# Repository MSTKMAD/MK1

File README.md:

# MK1

Migracion desde Bitbucket del repostorio de la Machete MK1

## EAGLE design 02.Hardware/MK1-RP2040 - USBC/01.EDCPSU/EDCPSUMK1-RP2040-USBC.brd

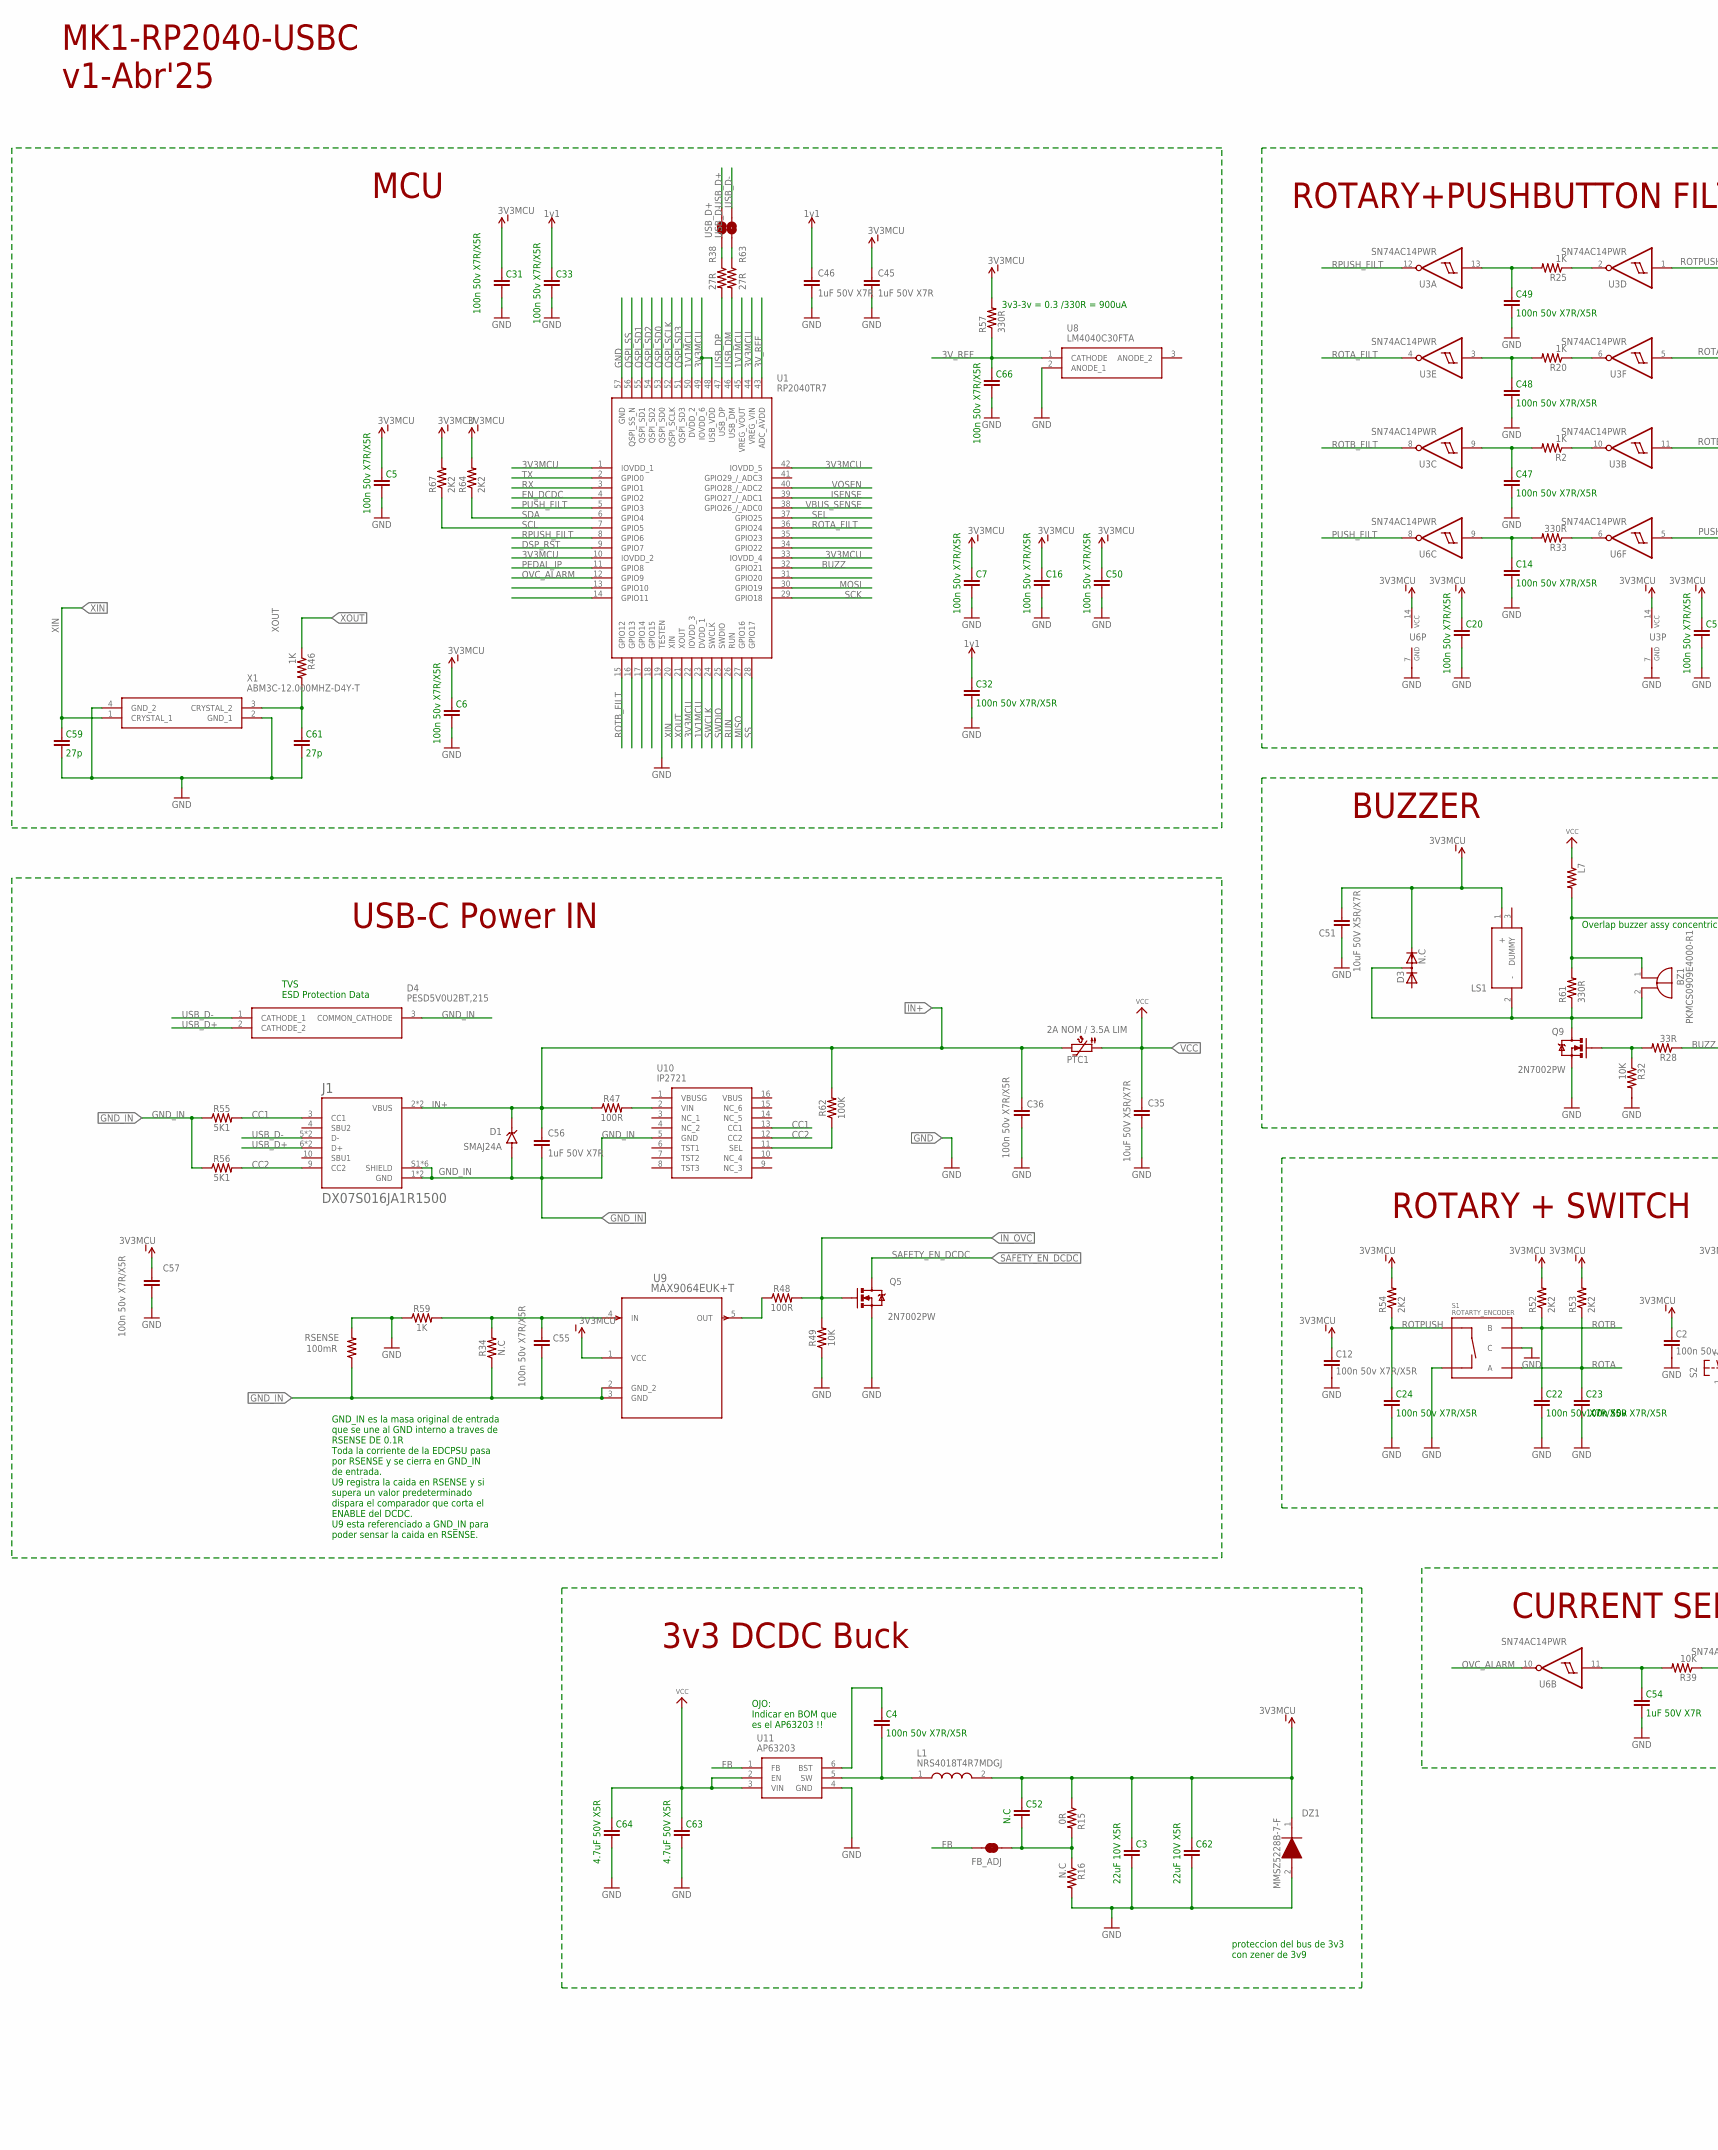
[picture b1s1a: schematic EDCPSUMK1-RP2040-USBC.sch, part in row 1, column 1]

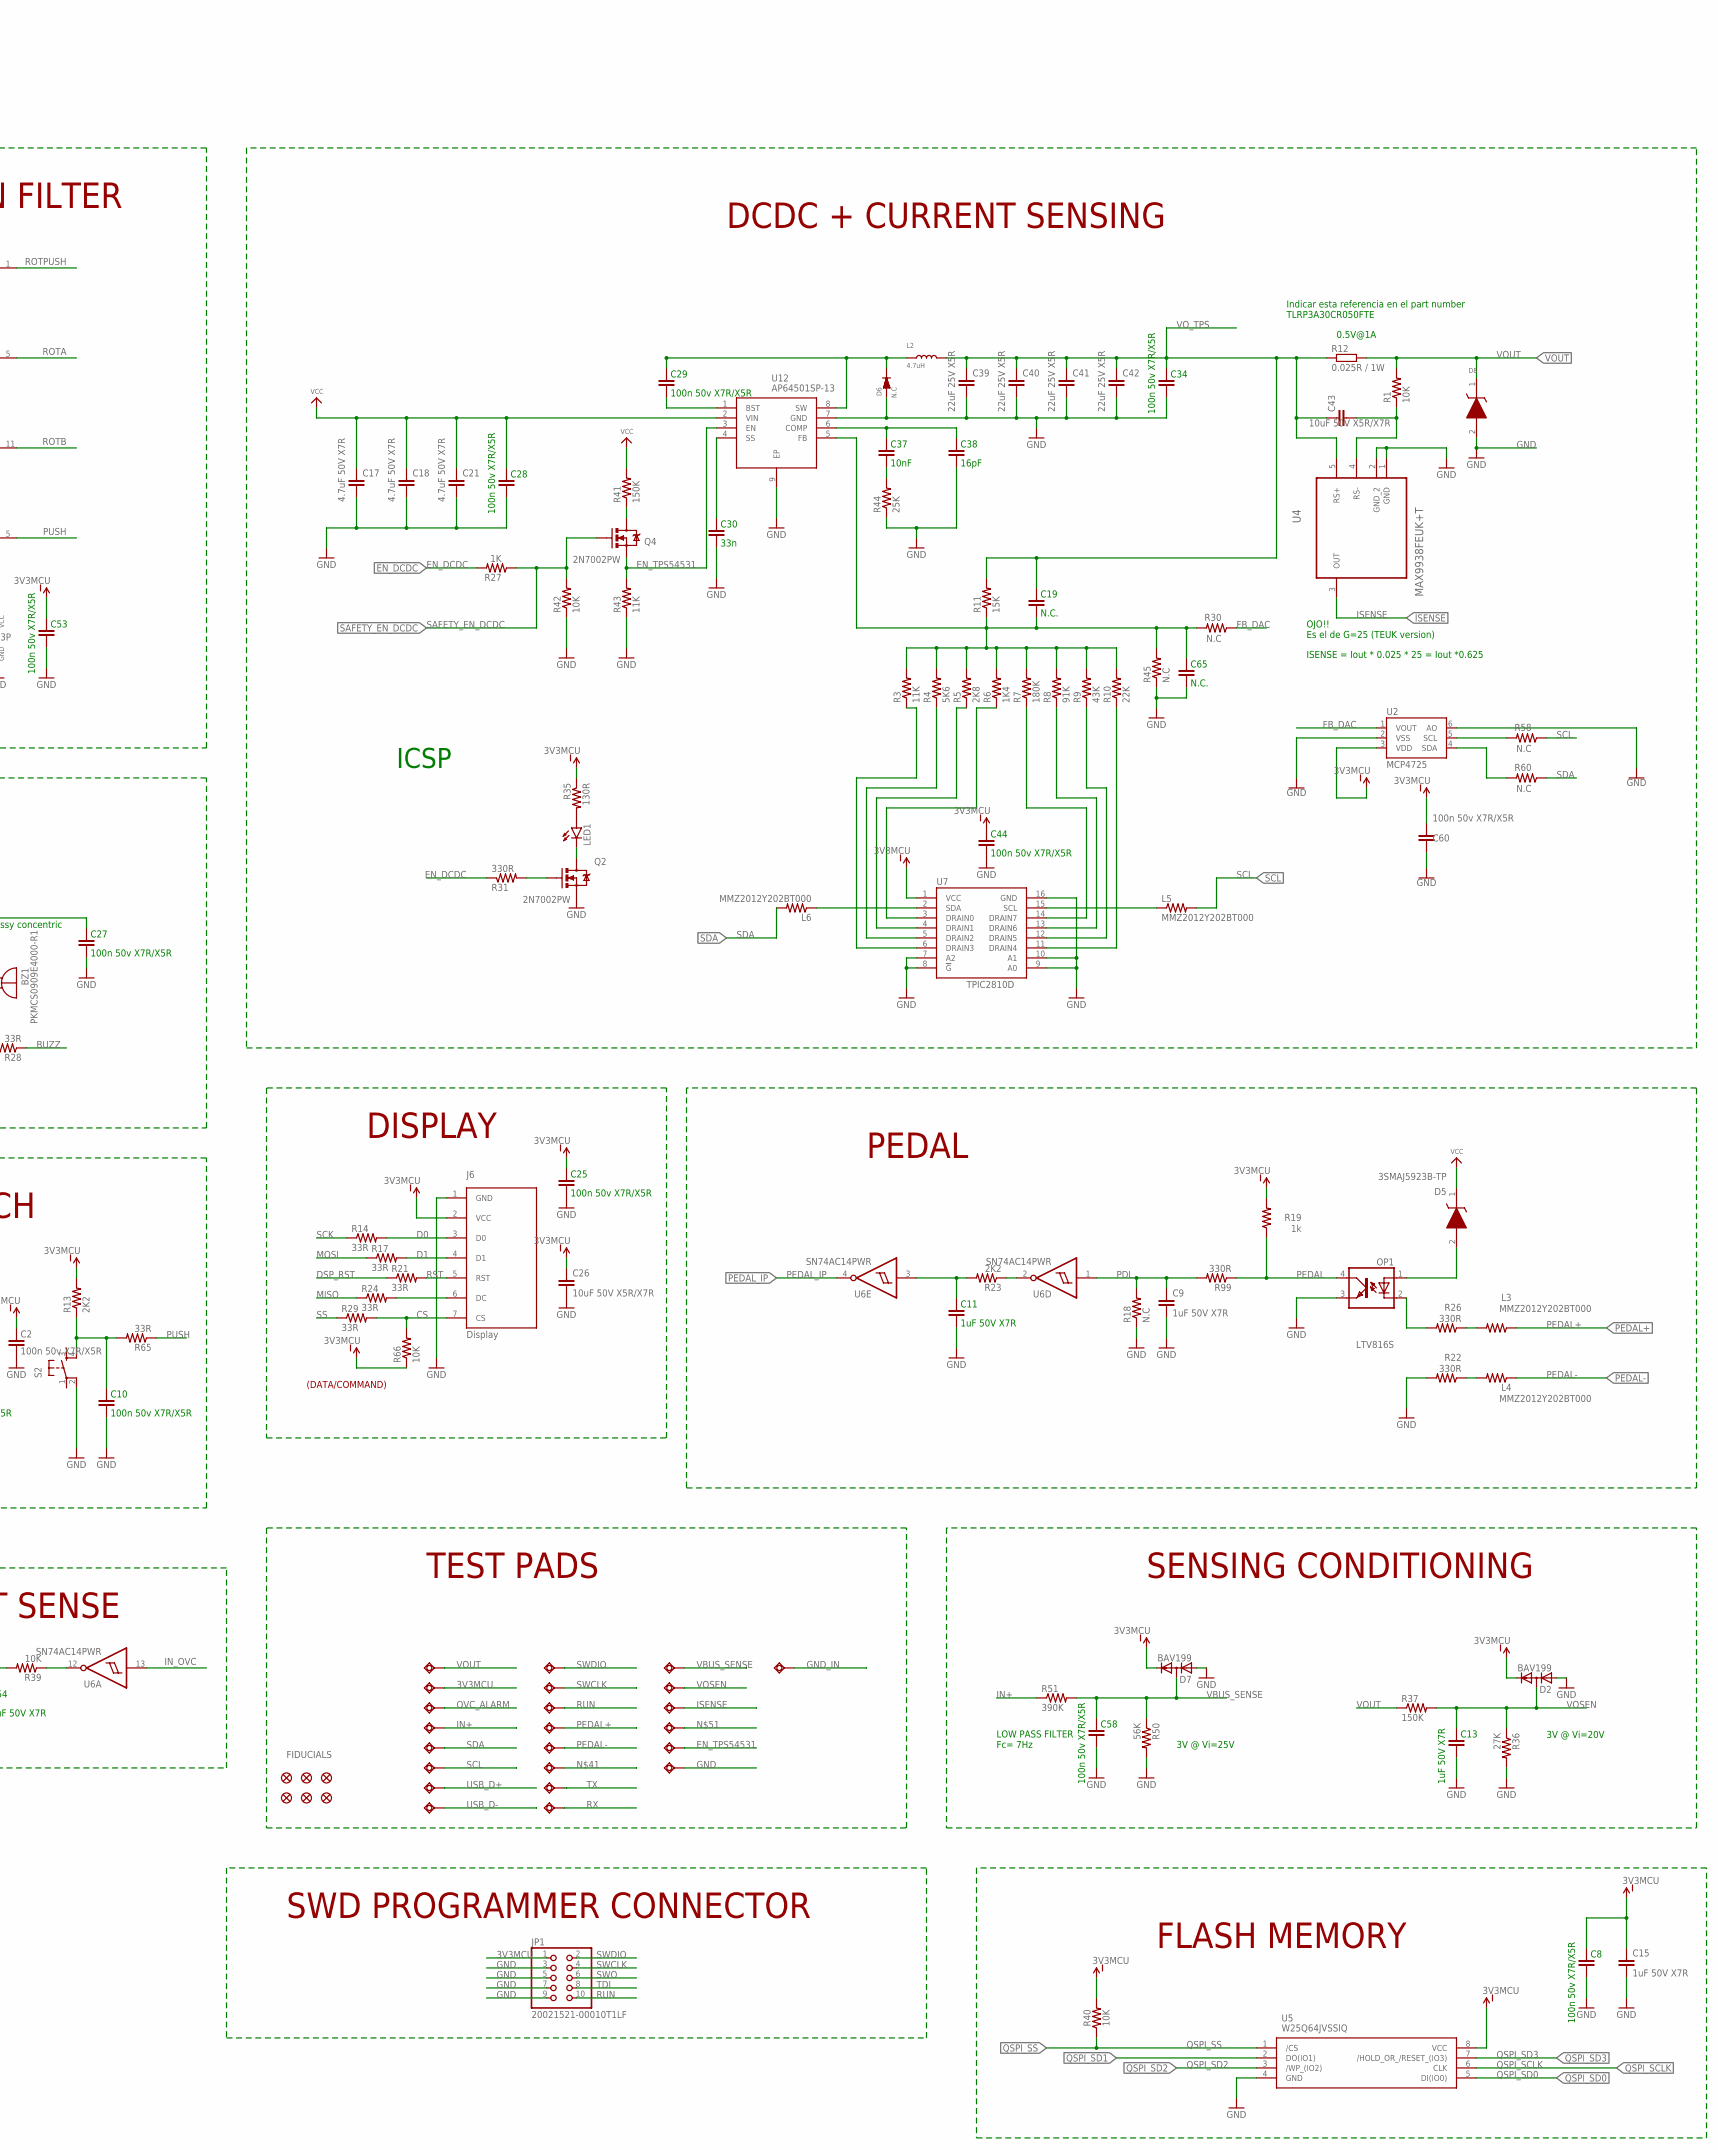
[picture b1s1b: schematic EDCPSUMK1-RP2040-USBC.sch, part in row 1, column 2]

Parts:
3V3MCU: TESTPAD_TPSQB1,27; TESTPAD_B1,27
BZ1: PKMCS0909E4000-R1; PKMCS0909
C2, C4, C5, C6, C7, C8, C10, C12, C14, C16, C20, C22, C23, C24, C25, C27, C28, C29, C31, C32, C33, C34, C36, C44, C47, C48, C49, C50, C53, C55, C57, C58, C60, C66: 100n 50v X7R/X5R; 0805
C3, C62: 22uF 10V X5R; 0805
C9, C11, C13, C15, C45, C46, C54, C56: 1uF 50V X7R; 0805
C17, C18, C21: 4.7uF 50V X7R; 1210
C19, C65: N.C.; 0805
C26, C35, C43, C51: 10uF 50V X5R/X7R; 1206
C30: 33n; 0805
C37: 10nF; 0805
C38: 16pF; 0805
C39, C40, C41, C42: 22uF 25V X5R; 1210
C52: N.C; 0805
C59, C61: 27p; 0805
C63, C64: 4.7uF 50V X5R; 0805
D1: SMAJ24A; DIOM4325X244N
D2, D7: BAV199; SOT23
D3: N.C; SOT23
D4: PESD5V0U2BT,215; SOT95P230X110-3N
D5: 3SMAJ5923B-TP; DIOM5226X244N
D6: N.C; DO-214AB
D8: RB060M-60TR; DIOM5226X244N
DZ1: MMSZ5228B-7-F; SODFL3518X115N
EN_TPS54531: TESTPAD_TPSQB1,27; TESTPAD_B1,27
FB_ADJ: JUMPER-SMT_2_NC_TRACE_NO-SILK; SMT-JUMPER_2_NC_TRACE_NO-SILK
FID1, FID2, FID3, FID4, FID5, FID6: FIDUCIAL1X2; FIDUCIAL-1X2
GND: TESTPAD_TPSQB1,27; TESTPAD_B1,27
GND_IN: TESTPAD_TPSQB1,27; TESTPAD_B1,27
IN+: TESTPAD_TPSQB1,27; TESTPAD_B1,27
ISENSE: TESTPAD_TPSQB1,27; TESTPAD_B1,27
J1: DX07S016JA1R1500; JAE_DX07S016JA1R1500
J6: Display; OLED_LCD
JP1: 20021521-00010T1LF
L1: NRS4018T4R7MDGJ; NRS4018T100MDGJ
L2: 4.7uH; WE-LHMI
L3, L4, L5, L6, L7: MMZ2012Y202BT000; 0805
LED1: LED3MM
LS1: SMT-0540-S-R; SMT0540SR
N$41, N$51: TESTPAD_TPSQB1,27; TESTPAD_B1,27
OP1: LTV816S; SMD4
OVC_ALARM: TESTPAD_TPSQB1,27; TESTPAD_B1,27
PEDAL+: TESTPAD_TPSQB1,27; TESTPAD_B1,27
PEDAL-: TESTPAD_TPSQB1,27; TESTPAD_B1,27
PTC1: 2A NOM / 3.5A LIM; 1812L
Q2, Q4, Q5, Q9: 2N7002PW; SOT323
R1, R32, R39, R40, R42, R49, R66: 10K; 0805
R2, R20, R25, R27, R46, R59: 1K; 0805
R3, R43: 11K; 0805
R4: 5K6; 0805
R5: 2K8; 0805
R6: 1K4; 0805
R7: 180K; 0805
R8: 91K; 0805
R9: 43K; 0805
R10: 22K; 0805
R11: 15K; 0805
R12: 0.025R / 1W; R2512
R13, R23, R52, R53, R54, R64, R67: 2K2; 0805
R14, R17, R21, R24, R28, R29, R65: 33R; 0805
R15: 0R; 0805
R16, R18, R30, R34, R45, R58, R60: N.C; 0805
R19: 1k; 0805
R22, R26, R31, R33, R57, R61, R99: 330R; 0805
R35: 130R; 0805
R36: 27K; 0805
R37, R41: 150K; 0805
R38, R63: 27R; 0805
R44: 25K; 0805
R47, R48: 100R; 0805
R50: 56K; 0805
R51: 390K; 0805
R55, R56: 5K1; 0805
R62: 100K; 0805
RSENSE: 100mR; 1206
RUN: TESTPAD_TPSQB1,27; TESTPAD_B1,27
RX: TESTPAD_TPSQB1,27; TESTPAD_B1,27
S1: ROTARTY_ENCODER; ROTARY_ENC_PLAIN
S2: TAC_SWITCH_KSC931G-SMD; TAC_SW_SMD_KSC931G
SCL: TESTPAD_TPSQB1,27; TESTPAD_B1,27
SDA: TESTPAD_TPSQB1,27; TESTPAD_B1,27
SWCLK: TESTPAD_TPSQB1,27; TESTPAD_B1,27
SWDIO: TESTPAD_TPSQB1,27; TESTPAD_B1,27
TX: TESTPAD_TPSQB1,27; TESTPAD_B1,27
U1: RP2040TR7
U2: MCP4725; SOT23-6
U3, U6: SN74AC14PWR; TSSOP14
U4: MAX9938FEUK+T; SOT95P280X145-5N
U5: W25Q64JVSSIQ; SOIC127P790X216-8N
U7: TPIC2810D; SO16
U8: LM4040C30FTA; SOT96P240X120-3N
U9: MAX9064EUK+T; 21-0057F_MXM
U10: IP2721; SOP65P640X120-16N
U11: AP63203; SOT95P280X100-6N
U12: AP64501SP-13; SOIC127P600X163-9N
USB-D+: TESTPAD_TPSQB1,27; TESTPAD_B1,27
USB-D-: TESTPAD_TPSQB1,27; TESTPAD_B1,27
USB_D+: JUMPER-SMT_2_NO_NO-SILK; SMT-JUMPER_2_NO_NO-SILK
USB_D-: JUMPER-SMT_2_NO_NO-SILK; SMT-JUMPER_2_NO_NO-SILK
VBUS_SENSE: TESTPAD_TPSQB1,27; TESTPAD_B1,27
VOSEN: TESTPAD_TPSQB1,27; TESTPAD_B1,27
VOUT: TESTPAD_TPSQB1,27; TESTPAD_B1,27
X1: ABM3C-12.000MHZ-D4Y-T; ABM3C16000MHZD4YT

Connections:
1V1MCU: C32.2, C33.2, C46.1, U1.23 (DVDD_1), U1.45 (VREG_VOUT), U1.50 (DVDD_2)
3V3MCU: 3V3MCU.TP, C2.2, C3.2, C5.2, C6.2, C7.2, C8.2, C12.2, C15.1, C16.2, C20.2, C25.2, C26.1, C31.2, C44.2, C45.1, C50.2, C51.2, C52.2, C53.2, C57.1, C60.2, C62.2, D2.2 (C), D3.2 (C), D7.2 (C), DZ1.1 (K), J6.2 (VCC), JP1.1, L1.2, LS1.1 (+), R13.2, R15.1, R19.2, R35.1, R40.2, R52.2, R53.2, R54.2, R57.2, R64.2, R66.1, R67.2, U1.1 (IOVDD_1), U1.10 (IOVDD_2), U1.22 (IOVDD_3), U1.33 (IOVDD_4), U1.42 (IOVDD_5), U1.44 (VREG_VIN), U1.48 (USB_VDD), U1.49 (IOVDD_6), U2.3 (VDD), U3.14 (VCC), U5.8 (VCC), U6.14 (VCC), U7.1 (VCC), U9.1 (VCC)
3V_REF: C66.2, R57.1, U1.43 (ADC_AVDD), U8.1 (CATHODE)
BUZZ: R28.1, U1.32 (GPIO21)
CC1: J1.3 (CC1), R55.2, U10.13 (CC1)
CC2: J1.9 (CC2), R56.2, U10.12 (CC2)
CS: J6.7 (CS), R29.2, R66.2
D0: J6.3 (D0), R14.2
D1: J6.4 (D1), R17.2
DSP_RST: R21.1, U1.9 (GPIO7)
EN_DCDC: R27.2, R31.1, U1.4 (GPIO2)
EN_TPS54531: EN_TPS54531.TP, Q4.2 (S), R43.2, U12.3 (EN)
FB: FB_ADJ.2, U11.1 (FB)
FB_DAC: R30.1, U2.1 (VOUT)
GND: C2.1, C3.1, C5.1, C6.1, C7.1, C8.1, C9.2, C10.1, C11.1, C12.1, C13.1, C14.1, C15.2, C16.1, C17.2, C18.2, C20.1, C21.2, C22.1, C23.1, C24.1, C25.1, C26.2, C27.1, C28.1, C30.1, C31.1, C32.1, C33.1, C34.1, C35.2, C36.1, C38.1, C39.2, C40.2, C41.2, C42.2, C44.1, C45.2, C46.2, C47.1, C48.1, C49.1, C50.1, C51.1, C53.1, C54.1, C57.2, C58.1, C59.1, C60.1, C61.1, C62.1, C63.1, C64.1, C65.1, C66.1, D2.1 (A), D6.1 (A), D7.1 (A), D8.2 (A), DZ1.2 (A), GND.TP, J6.1 (GND), JP1.3, JP1.5, JP1.7, JP1.9, OP1.3 (EMIT), Q2.2 (S), Q5.2 (S), Q9.2 (S), R16.2, R18.1, R22.2, R32.2, R36.2, R42.1, R43.1, R44.1, R45.1, R49.1, R50.2, R59.1, RSENSE.2, S1.C, S1.SW-, S2.2, U1.19 (TESTEN), U1.57 (GND), U2.2 (VSS), U2.6 (AO), U3.7 (GND), U4.1 (GND), U4.2 (GND_2), U5.4 (GND), U6.7 (GND), U7.7 (A2), U7.8 (!G), U7.9 (A0), U7.10 (A1), U7.16 (GND), U8.2 (ANODE_1), U11.4 (GND), U12.7 (GND), U12.9 (EP), X1.2 (GND_1), X1.4 (GND_2)
GND_IN: C55.2, C56.2, D1.A, D4.3 (COMMON_CATHODE), GND_IN.TP, J1.1 (GND), J1.12 (GND), J1.S1 (SHIELD), J1.S2 (SHIELD), J1.S3 (SHIELD), J1.S4 (SHIELD), J1.S5 (SHIELD), J1.S6 (SHIELD), R34.1, R55.1, R56.1, RSENSE.1, U9.2 (GND_2), U9.3 (GND), U10.5 (GND)
IN+: C36.2, C56.1, D1.C (K), IN+.TP, J1.2 (VBUS), J1.11 (VBUS), PTC1.2, R47.1, R51.1, R62.2
IN_OVC: Q5.1 (G), R48.2, R49.2, U6.13 (I)
ISENSE: ISENSE.TP, U1.39 (GPIO27_/_ADC1), U4.3 (OUT)
MISO: R24.1, U1.27 (GPIO16)
MOSI: R17.1, U1.30 (GPIO19)
unnamed: R3.1, U7.6 (DRAIN3)
unnamed: R4.1, U7.5 (DRAIN2)
unnamed: R5.1, U7.4 (DRAIN1)
unnamed: R6.1, U7.3 (DRAIN0)
unnamed: R7.1, U7.14 (DRAIN7)
unnamed: J6.6 (DC), R24.2
unnamed: R8.1, U7.13 (DRAIN6)
unnamed: R9.1, U7.12 (DRAIN5)
unnamed: R10.1, U7.11 (DRAIN4)
unnamed: C43.2, R1.1, U4.4 (RS-)
unnamed: LED1.A, R35.2
unnamed: LED1.K (C), Q2.3 (D)
unnamed: R33.1, U6.6 (O)
unnamed: R62.1, U10.11 (SEL)
unnamed: R39.1, U6.12 (O)
unnamed: D5.2 (A), OP1.1 (A)
unnamed: C10.2, R13.1, R65.2, S2.4
unnamed: C47.2, R2.2, U3.9 (I)
unnamed: C19.1, C65.2, R3.2, R4.2, R5.2, R6.2, R7.2, R8.2, R9.2, R10.2, R11.1, R30.2, R45.2, U12.5 (FB)
unnamed: Q9.1 (G), R28.2, R32.1
unnamed: Q2.1 (G), R31.2
unnamed: R2.1, U3.10 (O)
unnamed: R20.1, U3.6 (O)
unnamed: R25.1, U3.2 (O)
unnamed: C49.2, R25.2, U3.13 (I)
unnamed: C48.2, R20.2, U3.3 (I)
unnamed: C11.2, R23.2, U6.3 (I)
unnamed: BZ1.2 (-), D3.3 (AC), LS1.2 (-), Q9.3 (D), R61.1
unnamed: BZ1.1 (+), C27.2, L7.2, R61.2
unnamed: R23.1, U6.2 (O)
unnamed: Q4.3 (D), R41.1
unnamed: C14.2, R33.2, U6.9 (I)
unnamed: C52.1, FB_ADJ.1, R15.2, R16.1
unnamed: C54.2, R39.2, U6.11 (I)
unnamed: L6.1, U7.2 (SDA)
unnamed: N$41.TP, OP1.2 (C), R26.2
unnamed: L3.2, R26.1
unnamed: C30.2, U12.4 (SS)
unnamed: R58.2, U2.5 (SCL)
unnamed: L4.2, R22.1
unnamed: C29.1, U12.1 (BST)
unnamed: R60.2, U2.4 (SDA)
unnamed: R47.2, U10.2 (VIN)
unnamed: C29.2, D6.2 (K), L2.1, N$51.TP, U12.8 (SW)
unnamed: C37.2, C38.2, U12.6 (COMP)
unnamed: C37.1, R44.2
unnamed: L5.1, U7.15 (SCL)
unnamed: C4.2, U11.6 (BST)
unnamed: R48.1, U9.5 (OUT)
unnamed: C55.1, R34.2, R59.2, U9.4 (IN)
unnamed: C61.2, R46.2, X1.3 (CRYSTAL_2)
unnamed: R38.1, USB_D+.1
unnamed: R63.1, USB_D-.1
unnamed: C4.1, L1.1, U11.5 (SW)
OVC_ALARM: OVC_ALARM.TP, U1.12 (GPIO9), U6.10 (O)
PDL: C9.1, R18.2, R99.2, U6.1 (I)
PEDAL: OP1.4 (COL), R19.1, R99.1
PEDAL+: L3.1, PEDAL+.TP
PEDAL-: L4.1, PEDAL-.TP
PEDAL_IP: U1.11 (GPIO8), U6.4 (O)
PUSH: R65.1, U6.5 (I)
PUSH_FILT: U1.5 (GPIO3), U6.8 (O)
QSPI_SCLK: U1.52 (QSPI_SCLK), U5.6 (CLK)
QSPI_SD0: U1.53 (QSPI_SD0), U5.5 (DI(IO0))
QSPI_SD1: U1.55 (QSPI_SD1), U5.2 (DO(IO1))
QSPI_SD2: U1.54 (QSPI_SD2), U5.3 (/WP_(IO2))
QSPI_SD3: U1.51 (QSPI_SD3), U5.7 (/HOLD_OR_/RESET_(IO3))
QSPI_SS: R40.1, U1.56 (QSPI_SS_N), U5.1 (/CS)
ROTA: C23.2, R53.1, S1.A, U3.5 (I)
ROTA_FILT: U1.36 (GPIO24), U3.4 (O)
ROTB: C22.2, R52.1, S1.B, U3.11 (I)
ROTB_FILT: U1.15 (GPIO12), U3.8 (O)
ROTPUSH: C24.2, R54.1, S1.SW+, U3.1 (I)
RPUSH_FILT: U1.8 (GPIO6), U3.12 (O)
RST: J6.5 (RST), R21.2
RUN: JP1.10, RUN.TP, U1.26 (RUN)
RX: RX.TP, U1.3 (GPIO1)
SAFETY_EN_DCDC: Q4.1 (G), Q5.3 (D), R27.1, R42.2
SCK: R14.1, U1.29 (GPIO18)
SCL: L5.2, R58.1, R67.1, SCL.TP, U1.7 (GPIO5)
SDA: L6.2, R60.1, R64.1, SDA.TP, U1.6 (GPIO4)
SEL: U1.37 (GPIO25)
SS: R29.1, U1.28 (GPIO17)
SWCLK: JP1.4, SWCLK.TP, U1.24 (SWCLK)
SWDIO: JP1.2, SWDIO.TP, U1.25 (SWDIO)
SWO: JP1.6
TDI: JP1.8
TX: TX.TP, U1.2 (GPIO0)
USB_D+: D4.2 (CATHODE_2), J1.6 (D+), J1.7 (D+), USB-D+.TP, USB_D+.2
USB_D-: D4.1 (CATHODE_1), J1.5 (D-), J1.8 (D-), USB-D-.TP, USB_D-.2
USB_DM: R63.2, U1.46 (USB_DM)
USB_DP: R38.2, U1.47 (USB_DP)
VBUS_SENSE: C58.2, D7.3 (AC), R50.1, R51.2, U1.38 (GPIO26_/_ADC0), VBUS_SENSE.TP
VCC: C17.1, C18.1, C21.1, C28.2, C35.1, C63.2, C64.2, D5.1 (K), L7.1, PTC1.1, R41.2, U11.2 (EN), U11.3 (VIN), U12.2 (VIN)
VOSEN: C13.2, D2.3 (AC), R36.1, R37.2, U1.40 (GPIO28_/_ADC2), VOSEN.TP
VOUT: D8.1 (K), R1.2, R12.2, R37.1, VOUT.TP
VO_TPS: C19.2, C34.2, C39.1, C40.1, C41.1, C42.1, C43.1, L2.2, R11.2, R12.1, U4.5 (RS+)
XIN: C59.2, U1.20 (XIN), X1.1 (CRYSTAL_1)
XOUT: R46.1, U1.21 (XOUT)

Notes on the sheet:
0.5V@1A
SENSING CONDITIONING
TEST PADS
MK1-RP2040-USBC v1-Abr'25
(DATA/COMMAND)
Overlap buzzer assy concentric
ICSP
BUZZER
ROTARY + SWITCH
DISPLAY
FIDUCIALS
OJO!! Es el de G=25 (TEUK version)
ISENSE = Iout * 0.025 * 25 = Iout *0.625
3V @ Vi=25V
LOW PASS FILTER Fc= 7Hz
SWD PROGRAMMER CONNECTOR
3v3 DCDC Buck
OJO: Indicar en BOM que es el AP63203 !!
FLASH MEMORY
USB-C Power IN
PEDAL
CURRENT SENSE
ROTARY+PUSHBUTTON FILTER
DCDC + CURRENT SENSING
MCU
Indicar esta referencia en el part number TLRP3A30CR050FTE
3v3-3v = 0.3 /330R = 900uA
TVS ESD Protection Data
GND_IN es la masa original de entrada que se une al GND interno a traves de RSENSE DE 0.1R Toda la corriente de la EDCPSU pasa por RSENSE y se cierra en GND_IN de entrada. U9 registra la caida en RSENSE y si supera un valor predeterminado dispara el comparador que corta el ENABLE del DCDC. U9 esta 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
proteccion del bus de 3v3 con zener de 3v9
3V @ Vi=20V

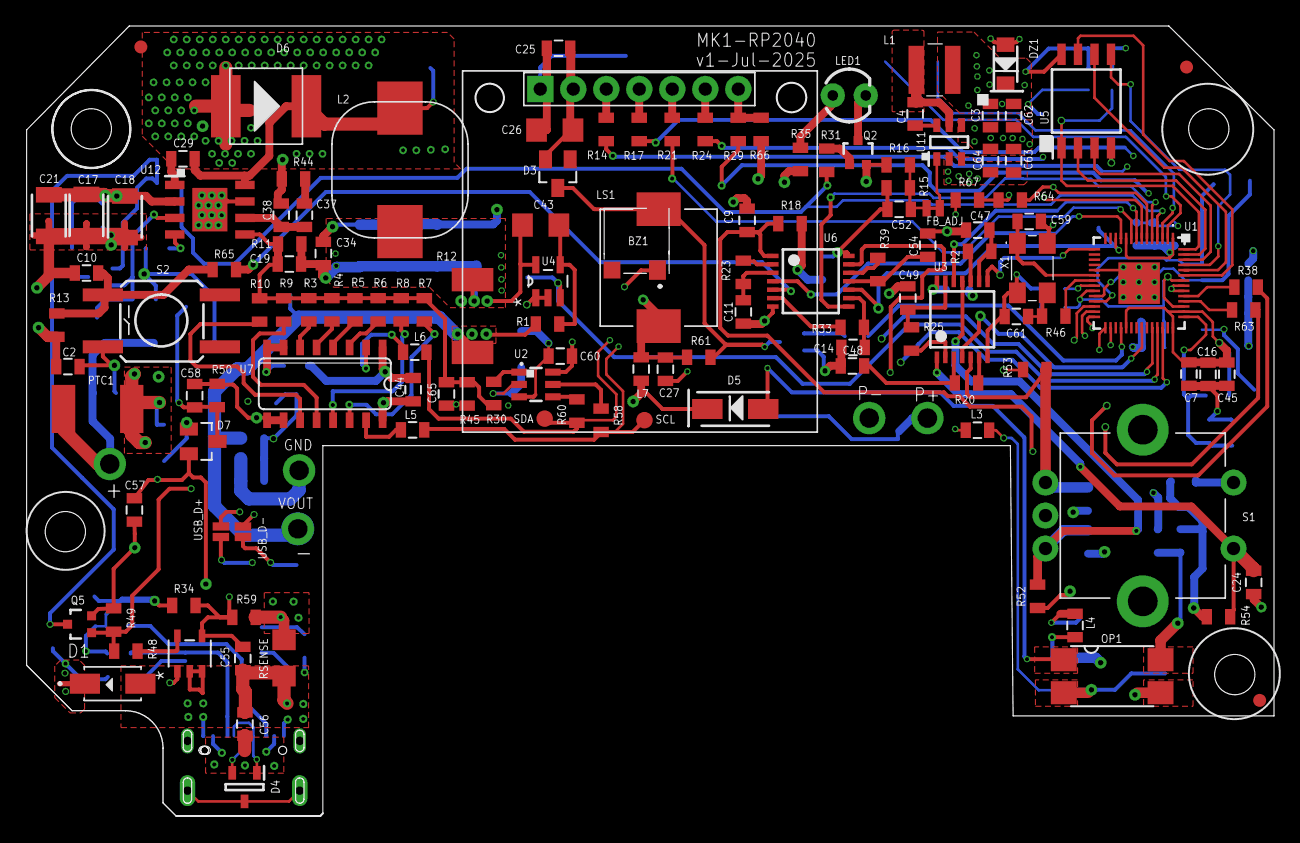
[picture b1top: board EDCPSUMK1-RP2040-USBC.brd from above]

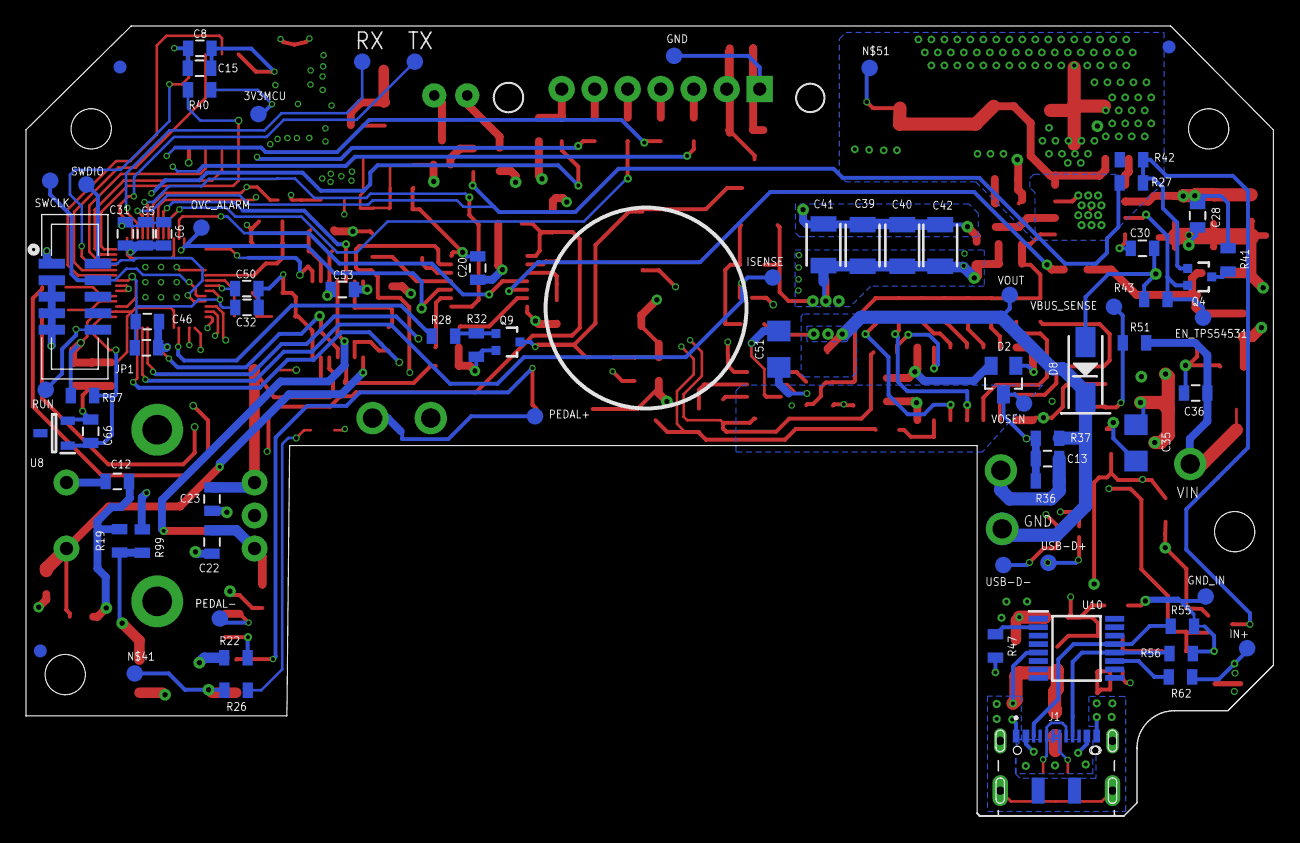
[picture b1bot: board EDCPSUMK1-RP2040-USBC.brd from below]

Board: 4 copper layers, 96.0 x 60.8 mm, 209 parts (76 on the bottom side), 117 nets.

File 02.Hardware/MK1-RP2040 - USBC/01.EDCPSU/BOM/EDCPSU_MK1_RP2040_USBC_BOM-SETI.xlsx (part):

|  |  |  | BOM VERSION v | 1
 |  |  |  | Fecha | 45839
 |  |  |  | MK1-RP2040-USBC
Assembly? | Cambios | Pos | Qty | Parts | Value | Device | Package | Description | Details | COST (500pcs) | COST per Board (500 pcs) | DIGIKEY
P | NO | 1 | 1 | BZ1 | PKMCS0909E4000-R1 | PKMCS0909E4000-R1 | PKMCS0909 | PKMCS0909E4000-R1 |  | 0.48 | 0.48 | https://www.digikey.es/es/products/detail/murata-electronics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
P | NO | 2 | 3 | C17, C18, C21 | 4.7uF 50V X7R | CAP1210 | SMD1210 | Capacitor |  | 0.10598 | 0.31794 | https://www.digikey.es/en/products/detail/samsung-electro-me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
NO | NO | 3 | 0 | C19, C65 | N.C. | CAP0805 | SMD0805 | Capacitor |  |  | 0
P | NO | 4 | 34 | C2, C4, C5, C6, C7, C8, C10, C12, C14, C16, C20, C22, C23, C24, C25, C27, C28, 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 | 100n 50v X7R/X5R | CAP0805 | SMD0805 | Capacitor |  |  | 0
P | NO | 5 | 4 | C26, C35, C43, C51 | 10uF 50V X5R/X7R | CAP1206 | SMD1206 | Capacitor |  | 6.9220000000000004E-2 | 0.27688000000000001 | https://www.digikey.es/en/products/detail/samsung-electro-me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
P | NO | 6 | 2 | C3, C62 | 22uF 10V X5R | CAP0805 | SMD0805 | Capacitor |  | 5.6300000000000003E-2 | 0.11260000000000001 | https://www.digikey.es/en/products/detail/murata-electronics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
P | NO | 7 | 1 | C30 | 33n | CAP0805 | SMD0805 | Capacitor |  |  | 0
P | NO | 8 | 1 | C37 | 10nF | CAP0805 | SMD0805 | Capacitor |  |  | 0
P | NO | 9 | 1 | C38 | 16pF | CAP0805 | SMD0805 | Capacitor |  |  | 0
P | NO | 10 | 4 | C39, C40, C41, C42 | 22uF 25V X5R | CAP1210 | SMD1210 | Capacitor |  | 0.12361999999999999 | 0.49447999999999998 | https://www.digikey.es/en/products/detail/samsung-electro-me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
NO | NO | 11 | 0 | C52 | N.C | CAP0805 | SMD0805 | Capacitor |  |  | 0
P | NO | 12 | 2 | C59, C61 | 27p | CAP0805 | SMD0805 | Capacitor |  |  | 0
P | NO | 13 | 2 | C63, C64 | 4.7uF 50V X5R | CAP0805 | SMD0805 | Capacitor |  | 4.2759999999999999E-2 | 8.5519999999999999E-2 | https://www.digikey.es/en/products/detail/murata-electronics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
P | NO | 14 | 8 | C9, C11, C13, C15, C45, C46, C54, C56 | 1uF 50V X7R | CAP0805 | SMD0805 | Capacitor |  |  | 0
P | NO | 15 | 1 | D1 | SMAJ24A | SMAJ24A | SMA-DO214 | ESD Suppressors / TVS Diodes 24volts 5uA 10.3 Amps UNI-Dir |  | 0.10872 | 0.10872 | https://www.digikey.es/en/products/detail/littelfuse-inc/SMA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
P | NO | 16 | 2 | D2, D7 | BAV199 | BAV199 | SOT23 | DIODE |  | 0.1145 | 0.22900000000000001 | https://www.digikey.es/es/products/detail/infineon-technolog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
P | NO | 17 | 1 | D4 | PESD5V0U2BT,215 | PESD5V0U2BT,215 | SOT23 | PESD5V0U2BT - Ultra low capacitance bidirectional double ESD protection diode |  | 0.17976 | 0.17976 | https://www.digikey.es/es/products/detail/nexperia-usa-inc/P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
P | NO | 18 | 1 | D5 | 3SMAJ5923B-TP | 3SMAJ5923B-TP | SMA-DO214 | Zener Diodes 3W 8.2V |  | 0.1181 | 0.1181 | https://www.digikey.es/es/products/detail/micro-commercial-c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
NO | NO | 19 | 0 | D6 | N.C | DSMC | DO-214AB |  |  |  | 0
P | NO | 20 | 1 | D8 | SMAJ18A | SMAJ18A | SMA-DO214 | TVS 18V 400W Unidirectional |  | 0.12508 | 0.12508 | https://www.digikey.es/en/products/detail/littelfuse-inc/SMA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
P | NO | 21 | 1 | DZ1 | MMSZ5228B | MMSZ5228B | SOD123F | Diode Zener 3.9 5% 500mW 2Pin SOD123 Diodes Inc MMSZ5227B-7-F Zener Diode, 3.9V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 |  | 8.6999999999999994E-2 | 8.6999999999999994E-2 | https://eu.mouser.com/ProductDetail/Diotec-Semiconductor/MMS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
P | NO | 22 | 1 | J1 | DX07S016JA1R1500 | DX07S016JA1R1500 | JAE_DX07S016JA1R1500 | USB-C (USB TYPE-C) USB 2.0 Receptacle Connector 24 (16+8 Dummy) Position Surfac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 |  | 1.0803 | 1.0803 | https://www.digikey.es/es/products/detail/jae-electronics/DX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
P | NO | 23 | 1 | J6 | Display | OLED_LCD | OLED_LCD |  |  |  | 0
P | NO | 24 | 1 | JP1 | 20021521-00010T1LF | 20021521-00010T1LF | 20021521-00010T1LF | MINITEK 127 SHROUDED HDR |  | 0.64117000000000002 | 0.64117000000000002 | https://www.digikey.es/en/products/detail/amphenol-cs-fci/20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
P | NO | 25 | 1 | L1 | NRS4018T4R7MDGJ | NRS4018T4R7MDGJ | NRS4018T100MDGJ | Inductor SMD wirewound 4.7uH |  | 0.12452000000000001 | 0.12452000000000001 | https://www.digikey.es/en/products/detail/taiyo-yuden/NRS401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
P | NO | 26 | 1 | L2 | 4.7uH | L74437368047 | WE-LHMI |  |  | 0.72116000000000002 | 0.72116000000000002 | https://www.digikey.es/en/products/detail/pulse-electronics/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
P | NO | 27 | 5 | L3, L4, L5, L6, L7 | MMZ2012Y202BT000 | SMD0805 | SMD0805 | Ferrite bead |  | 2.3E-2 | 0.11499999999999999 | https://www.digikey.es/en/products/detail/tdk-corporation/MM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
P | NO | 28 | 1 | LED1 | LTL1NHSH6D | LTL1NHSH6D | LTL1NHSH6D | LED 3MM LITEON YELLOW 65mcd 60º |  | 3.4189999999999998E-2 | 3.4189999999999998E-2 | https://www.tme.eu/es/en/details/ltl1nhsh6d/tht-leds-round/liteon/
NO | NO | 29 | 0 | LS1 | SMT-0540-S-R | SMT-0540-S-R | SMT0540SR | Speakers & Transducers SMD TRANSDUCER 3VP-P 100MA |  |  | 0
P | NO | 30 | 1 | OP1 | LTV816S | LTV816S | SMD4 | OPTO COUPLER |  | 0.1341 | 0.1341 | https://www.digikey.es/es/products/detail/liteon/LTV-816S/38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
P | NO | 31 | 1 | PTC1 | 2A NOM / 3.5A LIM | 0ZCC0150BF2C | SMD1812 | PTC RESTTBLE 1.50A 24V CHIP 1812 |  | 0.12822 | 0.12822 | https://www.digikey.es/es/products/detail/bel-fuse-inc/0ZCC0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
P | NO | 32 | 4 | Q2, Q4, Q5, Q9 | 2N7002PW | MOSFET-NCHANNEL2N7002PW | SOT323 | N-MOSFET VGS=2.4V 500mA, VDS=60V |  | 8.7800000000000003E-2 | 0.35120000000000001 | https://www.digikey.es/es/products/detail/nexperia-usa-inc/2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
P | NO | 33 | 7 | R1,R32, R39, R40, R42, R49, R66 | 10K | RESISTOR0805 | SMD0805 | Generic Resistor Package |  |  | 0
P | NO | 34 | 1 | R10 | 22K | RESISTOR0805 | SMD0805 | Generic Resistor Package |  |  | 0
P | NO | 35 | 1 | R12 | 0.025R / 1W | RR2512 | SMD2512 | 25mR Sensing resistor |  | 0.18551999999999999 | 0.18551999999999999 | https://www.digikey.es/en/products/detail/yageo/RL2512FK-070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
P | NO | 36 | 7 | R13, R23, R52, R53, R54, R64, R67 | 2K2 | RESISTOR0805 | SMD0805 | Generic Resistor Package |  |  | 0
P | NO | 37 | 7 | R14, R17, R21, R24, R28, R29, R65 | 33R | RESISTOR0805 | SMD0805 | Generic Resistor Package |  |  | 0
NO | NO | 38 | 7 | R16, R18, R30, R34, R45, R58, R60 | N.C | RESISTOR0805 | SMD0805 | Generic Resistor Package |  |  | 0
P | NO | 39 | 7 | R2, R19, R20, R25, R27, R46, R59 | 1K | RESISTOR0805 | SMD0805 | Generic Resistor Package |  |  | 0
P | NO | 40 | 7 | R22, R26, R31, R33, R61, R99, R57 | 330R | RESISTOR0805 | SMD0805 | Generic Resistor Package |  |  | 0
P | NO | 41 | 2 | R3, R43 | 11K | RESISTOR0805 | SMD0805 | Generic Resistor Package |  |  | 0
P | NO | 42 | 2 | R37, R41 | 150K | RESISTOR0805 | SMD0805 | Generic Resistor Package |  |  | 0
P | NO | 43 | 2 | R38, R63 | 27R | RESISTOR0805 | SMD0805 | Generic Resistor Package |  |  | 0
P | NO | 44 | 1 | R4 | 5K6 | RESISTOR0805 | SMD0805 | Generic Resistor Package |  |  | 0
P | NO | 45 | 1 | R36 | 27K | RESISTOR0805 | SMD0805 | Generic Resistor Package |  |  | 0
P | NO | 46 | 1 | R44 | 25K | RESISTOR0805 | SMD0805 | Generic Resistor Package |  |  | 0
P | NO | 47 | 2 | R47, R48 | 100R | RESISTOR0805 | SMD0805 | Generic Resistor Package |  |  | 0
P | NO | 48 | 1 | R5 | 2K8 | RESISTOR0805 | SMD0805 | Generic Resistor Package |  |  | 0
P | NO | 49 | 1 | R50 | 56K | RESISTOR0805 | SMD0805 | Generic Resistor Package |  |  | 0
P | NO | 50 | 1 | R51 | 390K | RESISTOR0805 | SMD0805 | Generic Resistor Package |  |  | 0
P | NO | 51 | 2 | R55, R56 | 5K1 | RESISTOR0805 | SMD0805 | Generic Resistor Package |  |  | 0
P | NO | 52 | 1 | R6 | 1K4 | RESISTOR0805 | SMD0805 | Generic Resistor Package |  |  | 0
P | NO | 53 | 1 | R62 | 100K | RESISTOR0805 | SMD0805 | Generic Resistor Package |  |  | 0
P | NO | 54 | 1 | R7 | 180K | RESISTOR0805 | SMD0805 | Generic Resistor Package |  |  | 0
P | NO | 55 | 1 | R8 | 91K | RESISTOR0805 | SMD0805 | Generic Resistor Package |  |  | 0
P | NO | 56 | 1 | R9 | 43K | RESISTOR0805 | SMD0805 | Generic Resistor Package |  |  | 0
P | NO | 57 | 1 | R35 | 130R | RESISTOR0805 | SMD0805 | Generic Resistor Package |  |  | 0
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
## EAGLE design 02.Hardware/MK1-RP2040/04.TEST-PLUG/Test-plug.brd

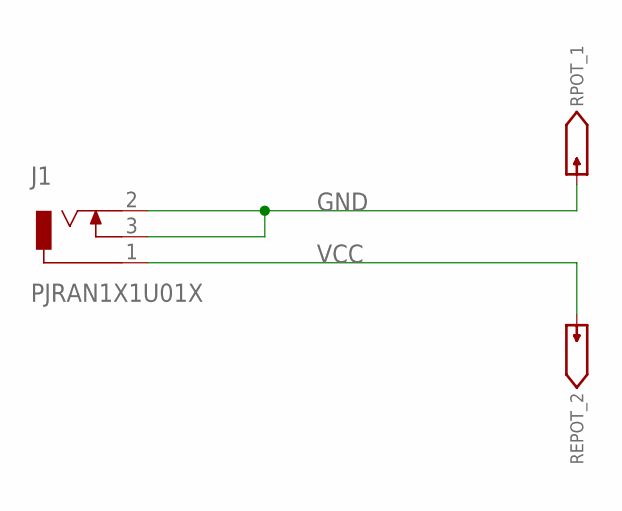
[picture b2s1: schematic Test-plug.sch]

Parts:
J1: PJRAN1X1U01X
REPOT_2: TESTPAD/W_HOLE_1X1; DIODE_GHI2_TESTPAD/W_HOLE_1X1
RPOT_1: TESTPAD/W_HOLE_1X1; DIODE_GHI2_TESTPAD/W_HOLE_1X1

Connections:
GND: J1.2, J1.3, RPOT_1.P$1
VCC: J1.1, REPOT_2.P$1

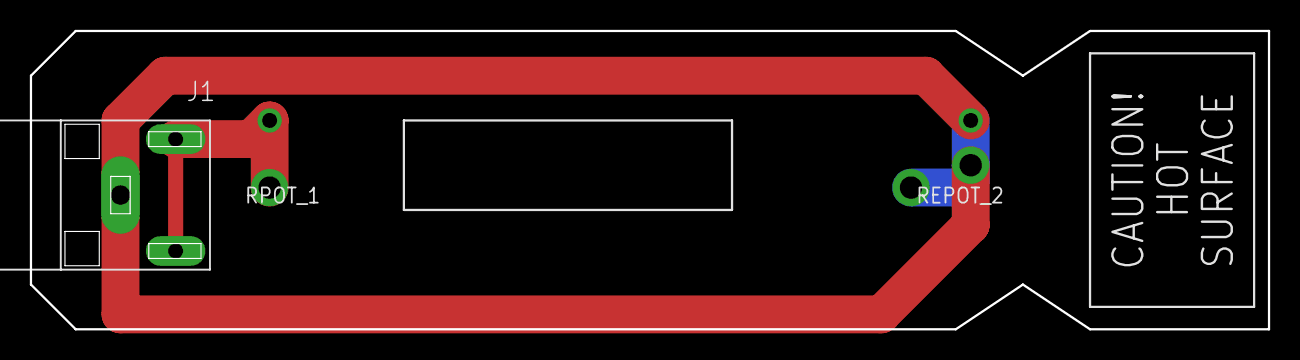
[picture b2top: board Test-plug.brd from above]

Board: 2 copper layers, 83.0 x 20.0 mm, 3 parts (0 on the bottom side), 2 nets.

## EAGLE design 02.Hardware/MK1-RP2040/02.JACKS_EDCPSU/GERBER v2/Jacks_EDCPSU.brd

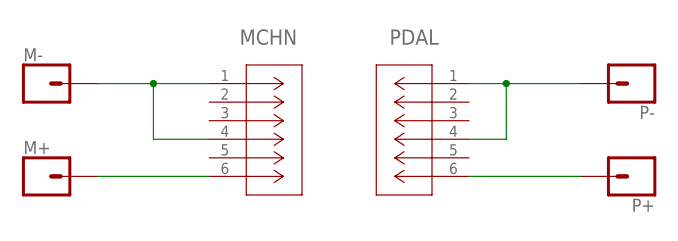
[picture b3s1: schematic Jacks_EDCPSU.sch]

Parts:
M+: CONN_01PTH_NO_SILK_KIT; 1X01NS_KIT
M-: CONN_01PTH_NO_SILK_KIT; 1X01NS_KIT
MCHN: ACJS-MHDR; CONN_MHDR_AMP
P+: CONN_01PTH_NO_SILK_KIT; 1X01NS_KIT
P-: CONN_01PTH_NO_SILK_KIT; 1X01NS_KIT
PDAL: ACJS-MHDR; CONN_MHDR_AMP

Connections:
unnamed: P-.1, PDAL.1, PDAL.4
unnamed: P+.1, PDAL.6
unnamed: M-.1, MCHN.1, MCHN.4
unnamed: M+.1, MCHN.6

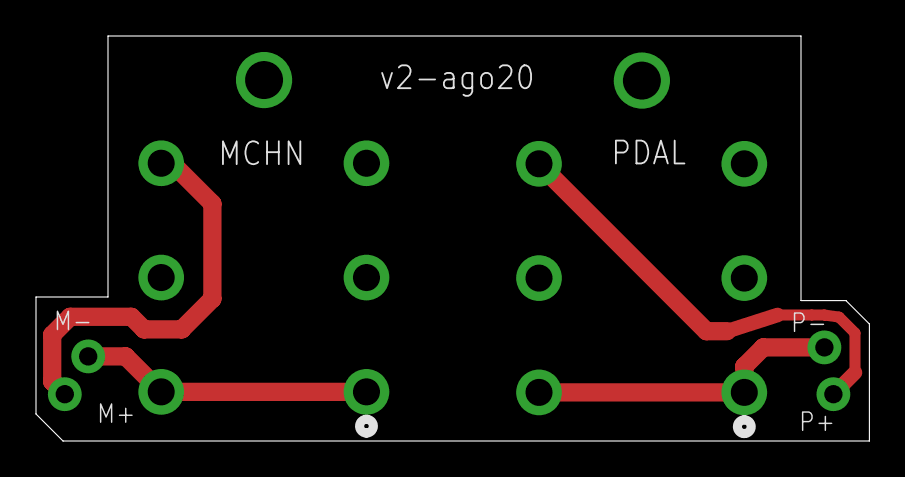
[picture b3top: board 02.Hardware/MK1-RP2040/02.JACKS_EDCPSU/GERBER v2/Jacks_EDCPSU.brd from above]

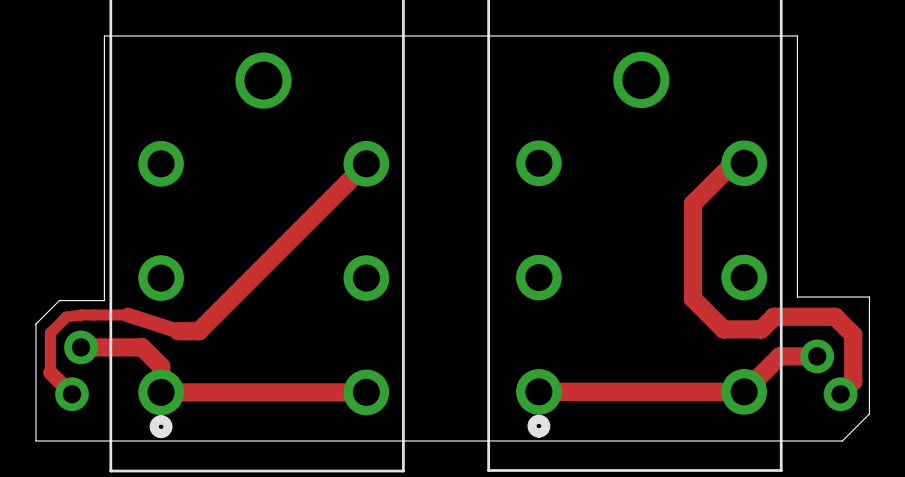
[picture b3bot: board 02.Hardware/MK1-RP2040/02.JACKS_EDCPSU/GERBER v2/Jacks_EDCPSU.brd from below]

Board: 2 copper layers, 46.3 x 22.5 mm, 6 parts (6 on the bottom side), 4 nets.

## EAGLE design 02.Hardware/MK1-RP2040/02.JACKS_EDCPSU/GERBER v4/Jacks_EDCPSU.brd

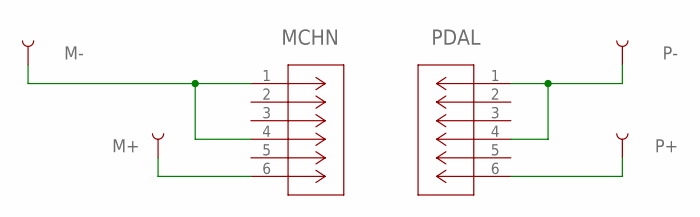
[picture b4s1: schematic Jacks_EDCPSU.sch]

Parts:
M+: TEST-POINT3; PAD.03X.03
M-: TEST-POINT3; PAD.03X.03
MCHN: ACJS-MHDR; CONN_MHDR_AMP
P+: TEST-POINT3; PAD.03X.03
P-: TEST-POINT3; PAD.03X.03
PDAL: ACJS-MHDR; CONN_MHDR_AMP

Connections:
unnamed: P-.P$1, PDAL.1, PDAL.4
unnamed: P+.P$1, PDAL.6
unnamed: M-.P$1, MCHN.1, MCHN.4
unnamed: M+.P$1, MCHN.6

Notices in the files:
parts and their libraries:
SparkFun-Connectors: Licensing: Creative Commons ShareAlike 4.0 International - https://creativecommons.org/licenses/by-sa/4.0
COPYRIGHT: Copyright (C) 2018 Accelerated Designs. All rights reserved
COPYRIGHT: Copyright (C) 2022 Ultra Librarian. All rights reserved.
